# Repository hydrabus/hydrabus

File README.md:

HydraBus
========

HydraBus an open source multi-tool hardware

You can Buy HydraBus/HydraNFC Online: http://hydrabus.com/buy-online

Wiki Getting Started: https://github.com/hydrabus/hydrafw/wiki/Getting-Started-with-HydraBus

HydraFW official firmware for Hydrabus
========

Wiki for HydraFW: https://github.com/hydrabus/hydrafw/wiki

See https://github.com/hydrabus/hydrafw

To build hydrafw see instructions here: 
* Windows: https://github.com/hydrabus/hydrafw/wiki/how-to-build-flash-and-use-hydrafw-on-windows
* Linux: https://github.com/hydrabus/hydrafw/wiki/how-to-build-flash-and-use-hydrafw-on-linux

Official Micro Python port for HydraBus
========
See https://github.com/micropython/micropython
Tested with GCC ARM 4.9 2015q3(GNU_ARM_4_9_2015q3) 
* See https://github.com/hydrabus/hydrafw_hydranfc_shield_v2/wiki `How to Build/Flash/Use HydraFW` for more details

To build micropython for HydraBus do:

    git clone --recursive https://github.com/micropython/micropython
    cd micropython/ports/stm32
    make BOARD=HYDRABUS

* At end of build you shall have:
 * GEN build-HYDRABUS/firmware.dfu
 * GEN build-HYDRABUS/firmware.hex
* In order to flash the *.dfu follow steps here: https://github.com/hydrabus/hydrafw/wiki/Getting-Started-with-HydraBus

For more details on official micropython hydrabus port see: https://github.com/micropython/micropython/tree/master/ports/stm32/boards/HYDRABUS

Official Black Magic JTAG/SWD debugger port for HydraBus
========
See https://github.com/blacksphere/blackmagic.git

Before to build the firmware check this issue (as you need a new GCC ARM Compiler >=4.9): https://github.com/blacksphere/blackmagic/issues/128
Tested with GCC ARM 4.9 2015q3(GNU_ARM_4_9_2015q3)
* See working version for reference blackmagic_branch_hydrabus_Firmware 1.5-00319-g49390fe-dirty.zip:
  * https://github.com/hydrabus/hydrabus/files/11436416/blackmagic_branch_hydrabus_Firmware.1.5-00319-g49390fe-dirty.zip
* Note: Latest version of blackmagic have "Device failed enumeration" issue see https://github.com/hydrabus/hydrabus/issues/4
* See https://github.com/hydrabus/hydrafw_hydranfc_shield_v2/wiki `How to Build/Flash/Use HydraFW` for more details

To build Black Magic for HydraBus do:

    git clone --recursive https://github.com/blacksphere/blackmagic.git
    cd blackmagic
    make PROBE_HOST=hydrabus

* At end of build you shall have:
 * OBJCOPY blackmagic.bin
 * OBJCOPY blackmagic.hex
 * Creating blackmagic.dfu
* In order to flash the *.dfu follow steps here: https://github.com/bvernoux/hydrafw/wiki/Getting-Started-with-HydraBus

For more details on official blackmagic hydrabus port see:
https://github.com/blacksphere/blackmagic/tree/master/src/platforms/hydrabus

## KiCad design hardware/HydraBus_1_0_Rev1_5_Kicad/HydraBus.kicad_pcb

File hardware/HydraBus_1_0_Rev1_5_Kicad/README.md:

HydraBus Schematic and Board KiCad (6.0.11)
========

This directory contains HydraBus Schematic and Board for KiCad (6.0.11)

HydraBus: Hardware license [CC BY-NC 4.0](https://creativecommons.org/licenses/by-nc/4.0/) (for commercial license contact info@hydrabus.com)

For more details on the hardware see also http://hydrabus.com/hydrabus-1-0-specifications

Revision 1.5 (vs Rev 1.4)
- HydraBus v1 Rev1.5 is designed under KiCad 6.0.11
- Replaced 2x microUSB connectors by 2x USB Female Type C connectors (Korean Hroparts Elec TYPE-C-31-M-12)
- Replacement of ESD protections (as old ones are obsolete)

To summarize there is no any functional change between HydraBus v1 Rev1.5 and previous versions

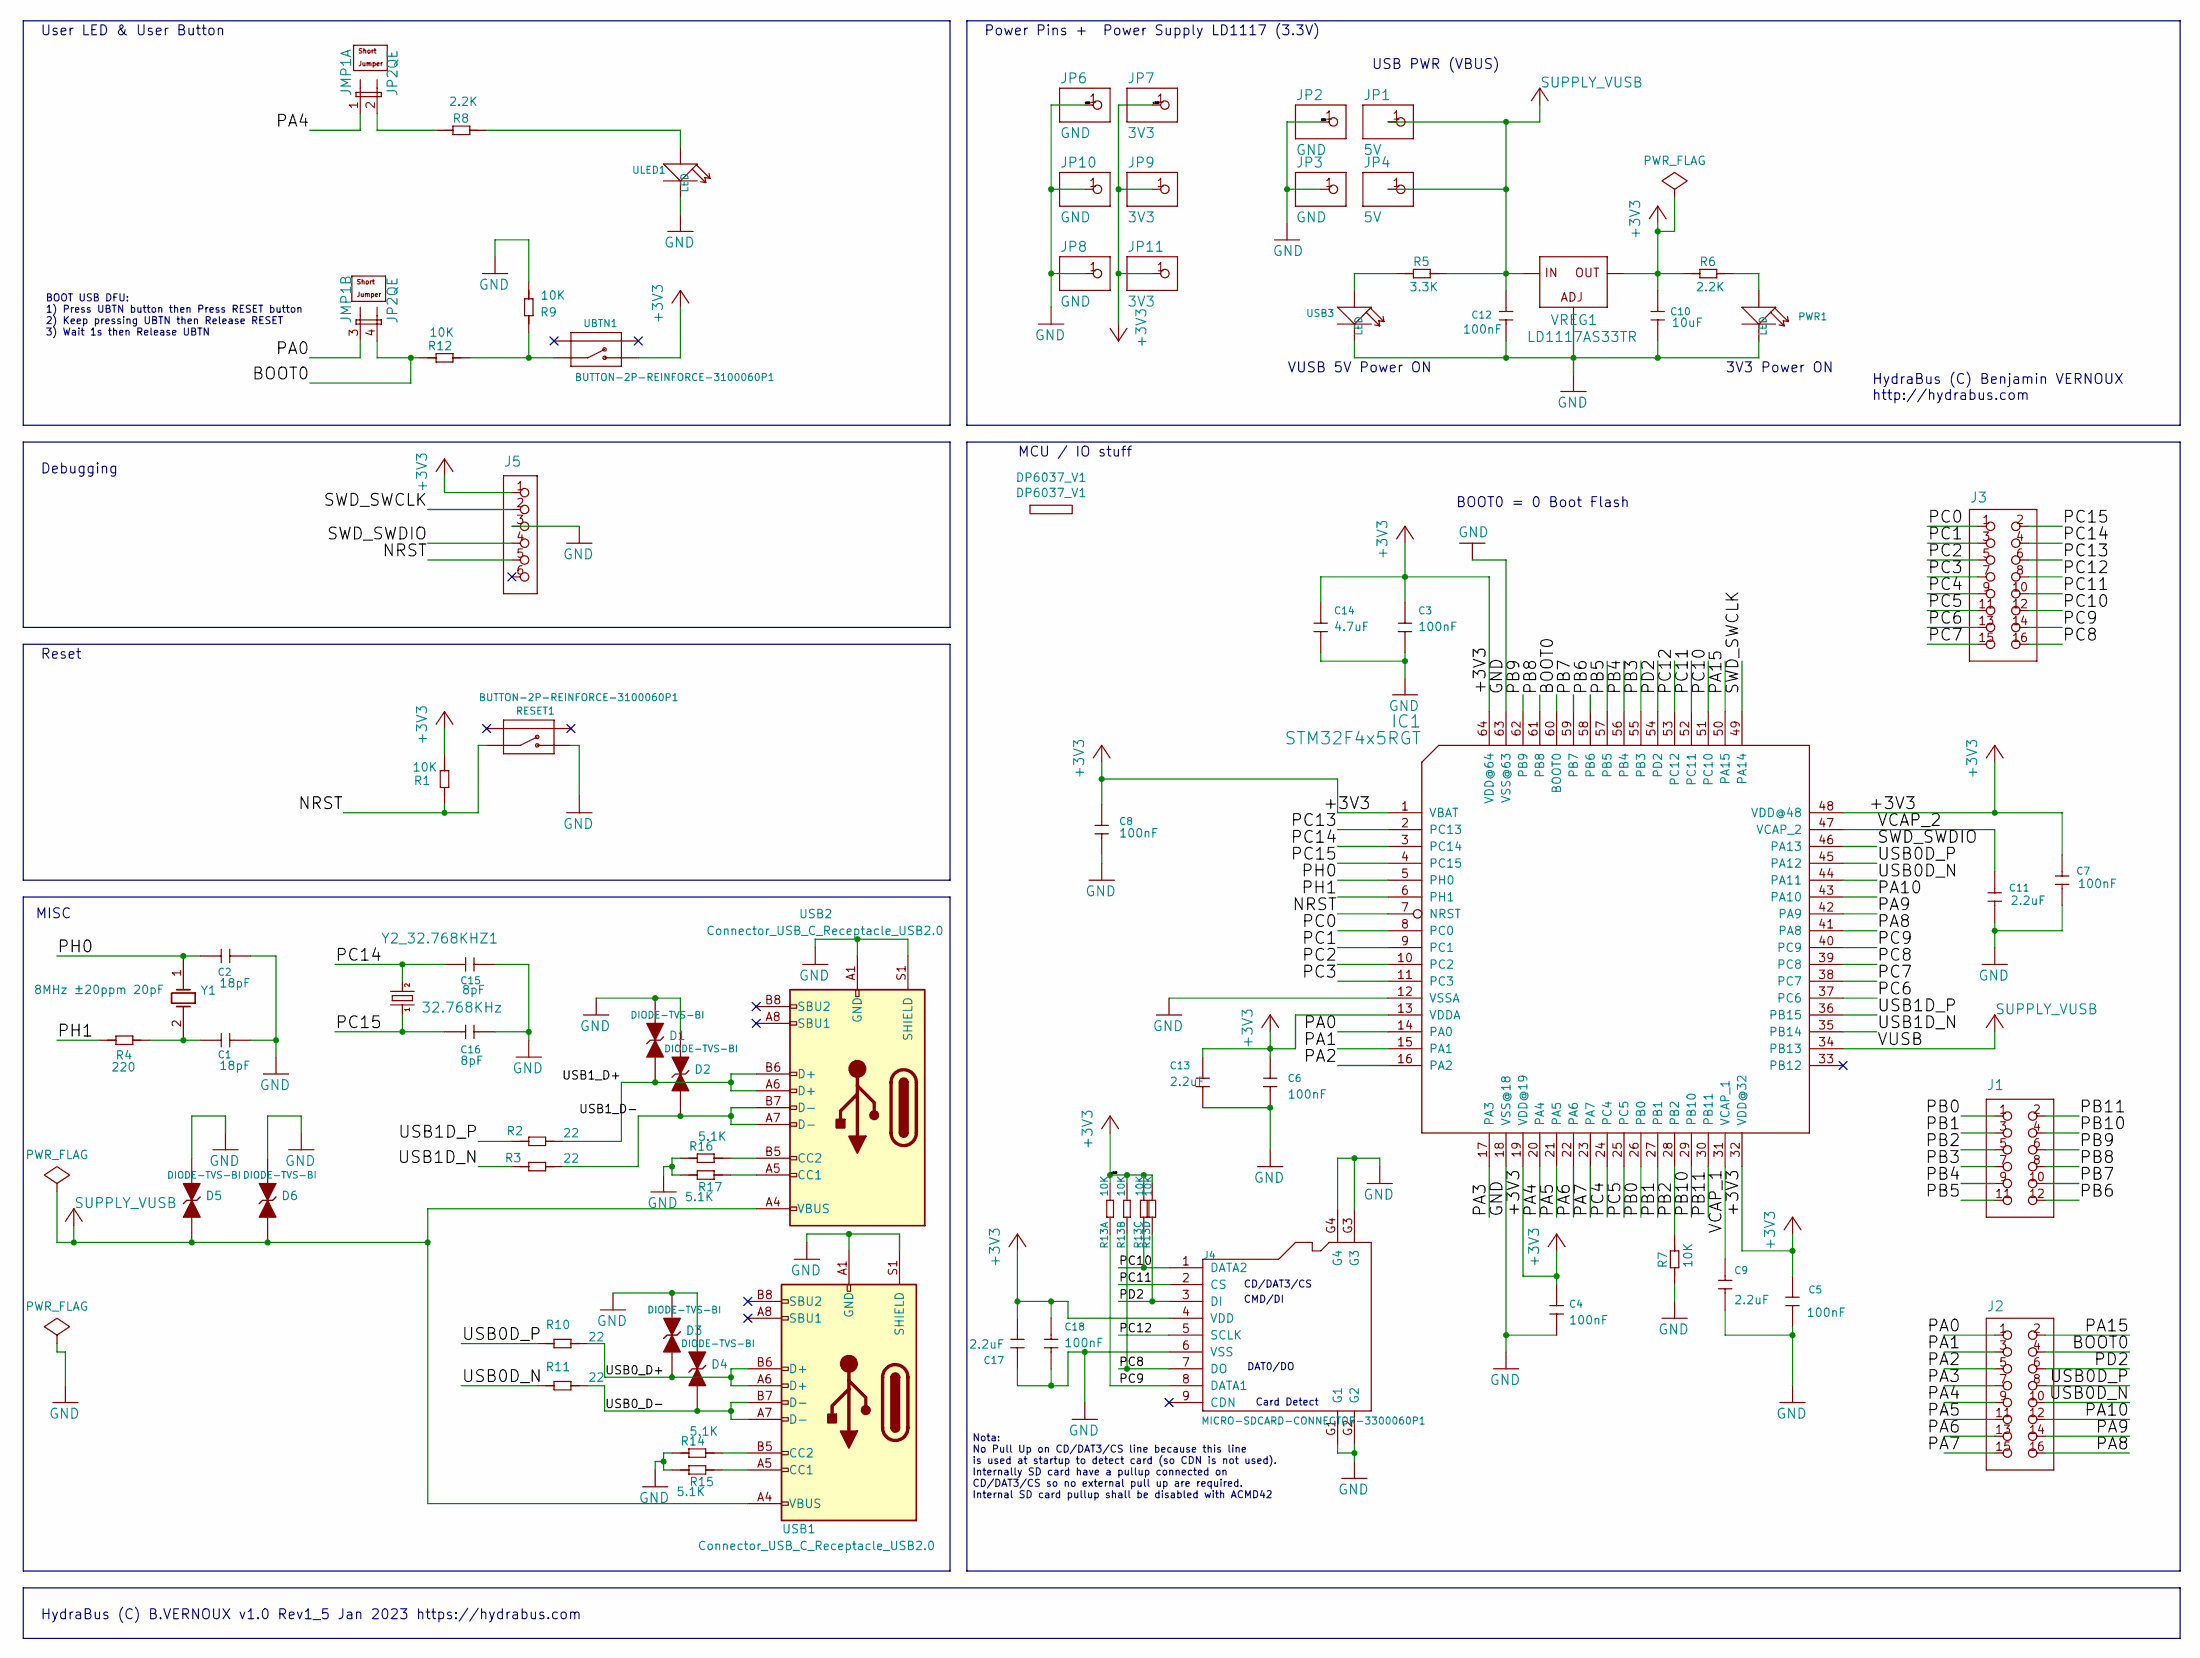
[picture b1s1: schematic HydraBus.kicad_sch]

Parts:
C1, C2: 18pF; C0603; LCSC_Part C1647
C3, C4, C5, C6, C7, C8, C12, C18: 100nF; C0603; LCSC_Part C14663
C9, C11, C13, C17: 2.2uF; C0603; LCSC_Part C23630
C10: 10uF; C0805; LCSC_Part C15850
C14: 4.7uF; C0603; LCSC_Part C19666
C15, C16: 8pF; C0603
D1, D2, D3, D4, D5, D6: DIODE-TVS-BI; 0402; LCSC_Part C191267
DP6037_V1: DP6037_V1
IC1: STM32F4x5RGT; LQFP64; LCSC_Part C15742
J1: CON_HEADER_2X07; M2X6; LCSC_Part PRPC007DFBN-RC
J2, J3: CON_HEADER_2X10; M2X8; LCSC_Part PRPC010DFBN-RC
J4: MICRO-SDCARD-CONNECTOR-3300060P1; 9P-SMD-W-RING; LCSC_Part C341092
J5: CON_HEADER_1X06-PTH; M1X6; LCSC_Part PEC06SFBN
JMP1: JP2QE; JP2Q
JMP_UBTN1: SHORT-JUMPER-2P-3460440P1; 2P-2.54
JMP_ULED1: SHORT-JUMPER-2P-3460440P1; 2P-2.54
JP1, JP4: 5V; 1X01
JP2, JP3, JP6, JP8, JP10: GND; 1X01
JP7, JP9, JP11: 3V3; 1X01
PWR1: LED; LED0603; LCSC_Part C72043
R1, R7, R9, R12: 10K; R0603; LCSC_Part C25804
R2, R3, R10, R11: 22; R0603; LCSC_Part C23345
R4: 220; R0603; LCSC_Part C22962
R5: 3.3K; R0603; LCSC_Part C22978
R6, R8: 2.2K; R0603; LCSC_Part C4190
R13: 10K; R1206-8; LCSC_Part C29718
R14, R15, R16, R17: 5.1K; R0603; LCSC_Part C23186
RESET1: BUTTON-2P-REINFORCE-3100060P1; 4P-SMD-7.0X3.5X3.5H-90D
UBTN1: BUTTON-2P-REINFORCE-3100060P1; 4P-SMD-7.0X3.5X3.5H-90D
ULED1: LED; LED0603; LCSC_Part C72043
USB1, USB2: Connector_USB_C_Receptacle_USB2.0; TYPE-C-31-M-12; LCSC_Part C165948
USB3: LED; LED0603; LCSC_Part C72043
VREG1: LD1117AS33TR; SOT223; LCSC_Part C115288
Y1: SMD-5032_2P_8MHz_20ppm_20pF; SMD-5032_2P; LCSC_Part C115962
Y2_32.768KHZ1: 32.768KHz; TC38H

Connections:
/BOOT0: IC1.60 (BOOT0), J2.4, JMP1.4 (2), R12.2
/NRST: IC1.7 (NRST), J5.5, R1.1, RESET1.1
/PA0: IC1.14 (PA0), J2.1, JMP1.3 (1)
/PA1: IC1.15 (PA1), J2.3
/PA2: IC1.16 (PA2), J2.5
/PA3: IC1.17 (PA3), J2.7
/PA4: IC1.20 (PA4), J2.9, JMP1.1
/PA5: IC1.21 (PA5), J2.11
/PA6: IC1.22 (PA6), J2.13
/PA7: IC1.23 (PA7), J2.15
/PA8: IC1.41 (PA8), J2.16
/PA9: IC1.42 (PA9), J2.14
/PA10: IC1.43 (PA10), J2.12
/PA15: IC1.50 (PA15), J2.2
/PB0: IC1.26 (PB0), J1.1
/PB1: IC1.27 (PB1), J1.3
/PB2: IC1.28 (PB2), J1.5, R7.1
/PB3: IC1.55 (PB3), J1.7
/PB4: IC1.56 (PB4), J1.9
/PB5: IC1.57 (PB5), J1.11
/PB6: IC1.58 (PB6), J1.12
/PB7: IC1.59 (PB7), J1.10
/PB8: IC1.61 (PB8), J1.8
/PB9: IC1.62 (PB9), J1.6
/PB10: IC1.29 (PB10), J1.4
/PB11: IC1.30 (PB11), J1.2
/PC0: IC1.8 (PC0), J3.1
/PC1: IC1.9 (PC1), J3.3
/PC2: IC1.10 (PC2), J3.5
/PC3: IC1.11 (PC3), J3.7
/PC4: IC1.24 (PC4), J3.9
/PC5: IC1.25 (PC5), J3.11
/PC6: IC1.37 (PC6), J3.13
/PC7: IC1.38 (PC7), J3.15
/PC8: IC1.39 (PC8), J3.16, J4.7 (DO), R13.2 (1)
/PC9: IC1.40 (PC9), J3.14, J4.8 (DATA1), R13.1
/PC10: IC1.51 (PC10), J3.12, J4.1 (DATA2), R13.3 (1)
/PC11: IC1.52 (PC11), J3.10, J4.2 (CS)
/PC12: IC1.53 (PC12), J3.8, J4.5 (SCLK)
/PC13: IC1.2 (PC13), J3.6
/PC14: C15.1, IC1.3 (PC14), J3.4, Y2_32.768KHZ1.2
/PC15: C16.1, IC1.4 (PC15), J3.2, Y2_32.768KHZ1.1
/PD2: IC1.54 (PD2), J2.6, J4.3 (DI), R13.4 (1)
/PH0: C2.1, IC1.5 (PH0), Y1.1 (OSC1)
/PH1: IC1.6 (PH1), R4.2
/SWD_SWCLK: IC1.49 (PA14), J5.2
/SWD_SWDIO: IC1.46 (PA13), J5.4
/USB0D_N: IC1.44 (PA11), J2.10, R11.2
/USB0D_P: IC1.45 (PA12), J2.8, R10.2
/USB0_D+: D3.1 (A), R10.1, USB1.A6 (D+), USB1.B6 (D+)
/USB0_D-: D4.1 (A), R11.1, USB1.A7 (D-), USB1.B7 (D-)
/USB1D_N: IC1.35 (PB14), R3.2
/USB1D_P: IC1.36 (PB15), R2.2
/USB1_D+: D1.1 (A), R2.1, USB2.A6 (D+), USB2.B6 (D+)
/USB1_D-: D2.1 (A), R3.1, USB2.A7 (D-), USB2.B7 (D-)
/VCAP_1: C9.2, IC1.31 (VCAP_1)
/VCAP_2: C11.1, IC1.47 (VCAP_2)
unnamed: C1.1, R4.1, Y1.2 (OSC2)
unnamed: JMP1.2, R8.2
unnamed: PWR1.+, R6.1
unnamed: R5.2, USB3.+
unnamed: R8.1, ULED1.+
unnamed: R9.1, R12.1, UBTN1.1
unnamed: R14.1, USB1.B5 (CC2)
unnamed: R15.2, USB1.A5 (CC1)
unnamed: R16.1, USB2.B5 (CC2)
unnamed: R17.2, USB2.A5 (CC1)
VBUS: C12.1, D5.1 (A), D6.1 (A), IC1.34 (PB13), JP1.1, JP4.1, R5.1, USB1.A4 (VBUS), USB1.A9 (VBUS), USB1.B4 (VBUS), USB1.B9 (VBUS), USB2.A4 (VBUS), USB2.A9 (VBUS), USB2.B4 (VBUS), USB2.B9 (VBUS), VREG1.3 (IN)

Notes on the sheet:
Debugging
BOOT USB DFU: 1) Press UBTN button then Press RESET button 2) Keep pressing UBTN then Release RESET 3) Wait 1s then Release UBTN
Card Detect
HydraBus (C) Benjamin VERNOUX http://hydrabus.com
MCU / IO stuff
BOOT0 = 0 Boot Flash
3V3 Power ON
USB PWR (VBUS)
CMD/DI
VUSB 5V Power ON
CD/DAT3/CS
User LED & User Button
Reset
HydraBus (C) B.VERNOUX v1.0 Rev1_5 Jan 2023 https://hydrabus.com
Power Pins + Power Supply LD1117 (3.3V)
DAT0/DO
Nota: No Pull Up on CD/DAT3/CS line because this line is used at startup to detect card (so CDN is not used). Internally SD card have a pullup connected on CD/DAT3/CS so no external pull up are required. Internal SD card pullup shall be disabled with ACMD42
MISC

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
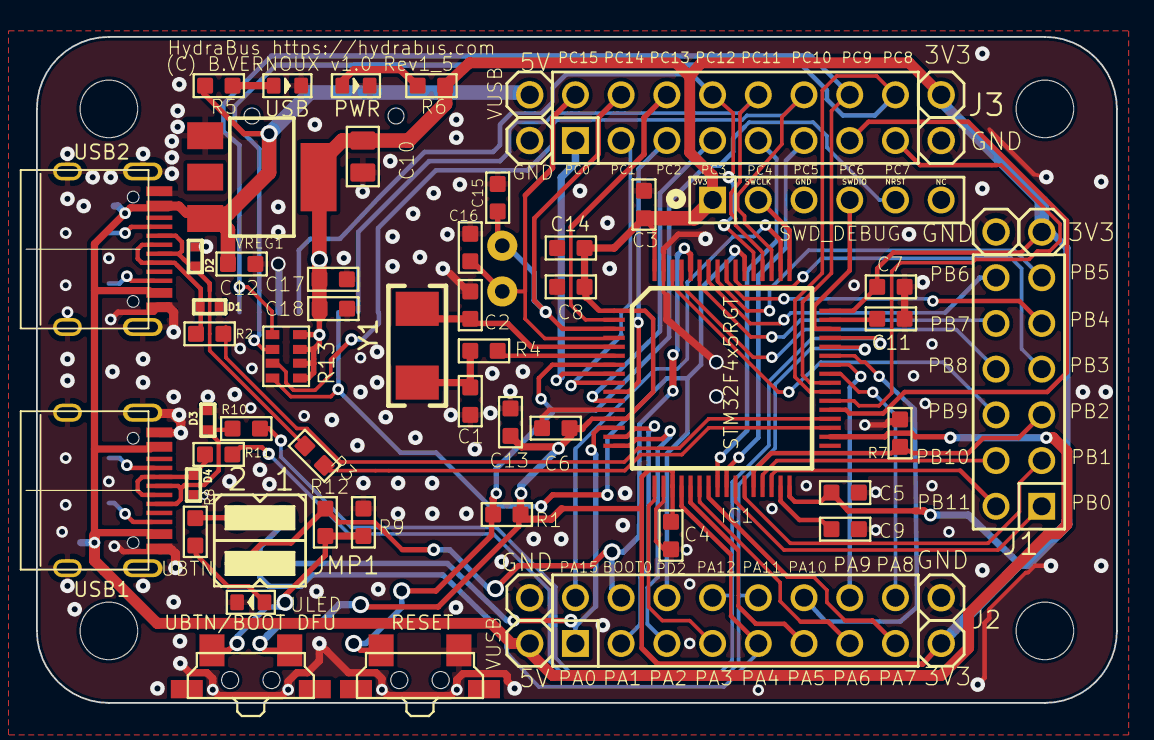
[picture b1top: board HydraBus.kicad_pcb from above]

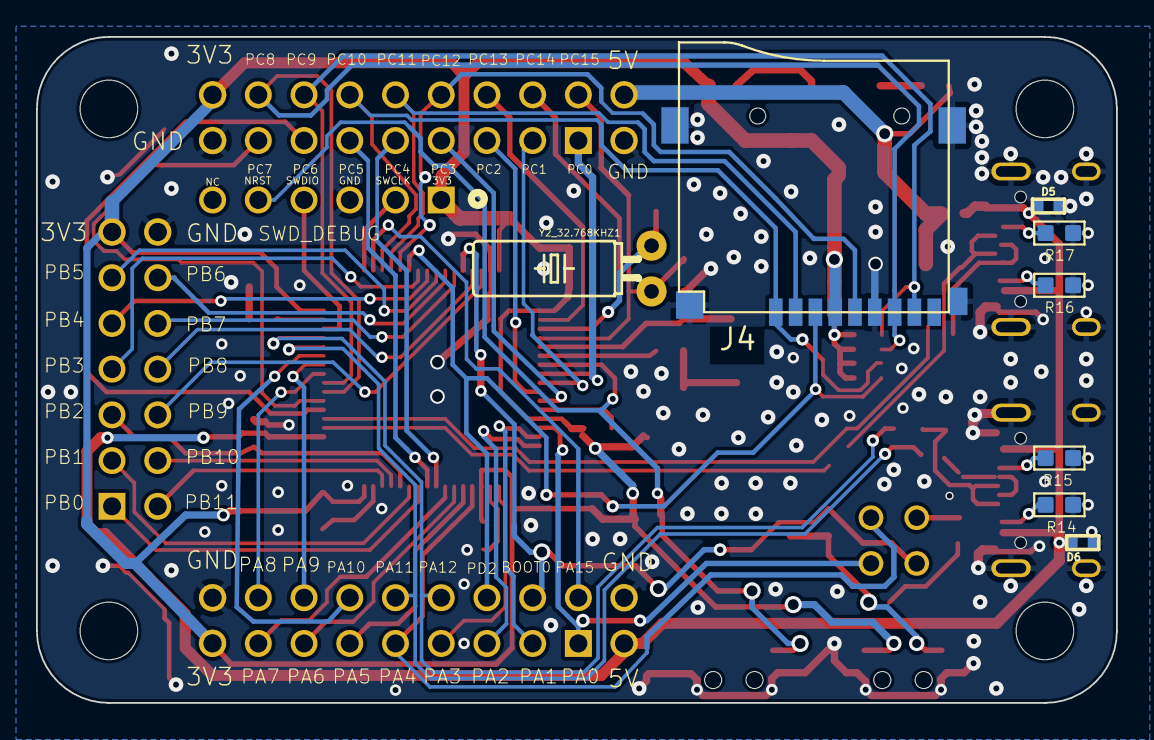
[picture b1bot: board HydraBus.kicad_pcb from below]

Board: 2 copper layers, 60.0 x 37.0 mm, 71 parts (8 on the bottom side), 70 nets.

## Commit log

2014-04-20 gitmodules update
2014-05-28 Update gitmodules
2014-05-28 Cleanup
2014-05-28 Cleanup gitmodule and added chibios 2.6.x
2014-06-02 HydraBus board
2014-06-22 Moved project/firmware to firmware directory
2014-09-11 HydraBus hardware files Eagle, PDF, xls ...
2014-09-11 Added MicroPython binary for HydraBus and instructions to flash it through USB DFU on HydraBus.
2014-09-11 Added board
2014-09-21 HydraFW first import version 0.1Beta
2014-09-21 Add picture for HydraBus to enter in USB DFU mode
2014-09-29 Update firmware from with last commit https://github.com/bvernoux/micropython/commit/41249e17c3a661dc36f49ff6156ce67a70466157
2014-09-30 HydraBus1.0 Sick Of Beige Case
2014-09-30 Windows XP, Vista, 7 and 8 drivers for HydraBus firmware USB CDC Virtual Serial Port.
2014-09-30 HydraBus1.0 Pin & Pin Assignment updated.
2014-10-01 Fix typo
2014-10-02 Added HydraBus Pins Assignment
2014-10-06 Add micropython firmware source as submodule.
2014-10-06 Add micropython firmware source as submodule and update with latest micropython.
2014-10-06 Cleanup Submodule micropython
2014-10-06 Add latest micropython as submodule
2014-10-06 Update micropython firmware to latest v1.3.3-31-g9c6f737
2014-10-07 Fixo typo thanks to Philippe Teuwen
    Update towards Philippe Teuwen wiki
    http://wiki.yobi.be/wiki/HydraNFC
2014-10-07 Fix for Debian... also exclude ModemManager thanks to Philippe Teuwen
2014-10-07 Fix typo thanks to Philippe Teuwen
    Update towards http://wiki.yobi.be/wiki/HydraNFC "Getting ready to use HydraBus" & "Using HydraBus"
2014-10-08 Cleanup, update configuration/conf and update microrl submodule.
2014-10-09 directory hydrafw deleted/replaced by submodule hydrafw
2014-10-10 Update hydrafw
2014-10-11 Added link to Wiki HydraFW
2014-10-13 Removed STM32F4_USB_DFU_Driver.zip
2014-10-22 Added HydraBus_1_0_HydraFW_Default_PinAssignment.odg/.pdf Fixed and update of HydraBus_1_0_PinAssignment.odg/.pdf
2014-10-22 Add A4 version of HydraBus_1_0_HydraFW_Default_PinAssignment
2014-10-22 Update link to latest hydrafw
2014-10-22 Updated submodule micropython to latest version
2014-10-22 update micropython firmware.dfu to latest version => Micro Python v1.3.3-113-g5fc42a6
2014-12-01 Added HydraBus Basic Pin Assignment
2014-12-26 Update micropython to latest Micro Python v1.3.3-340-gc55a4d8
2014-12-26 Update micropython to latest Micro Python v1.3.7-96-gc55a4d8
2014-12-26 Update hydrafw to latest version v0.4-beta-23-ge68b10a
2015-01-01 Updated Default Pin Assignment A4 and removed the old not A4.
2015-01-13 Added blackmagic port for HydraBus
2016-02-04 HydraBus v1.0 Rev1_2 Release (CadSoft Eagle v7.1 files + BOM + Schematic + Gerber)
2016-04-20 Update Black Magic official hydrabus port
2016-04-22 removed firmware link (obsolete)
2016-04-22 removed firmware link/submodule (obsolete)
2016-05-31 Add HydraBus_1_0_Shield_Template_Rev0 Kicad link
2016-12-06 HydraBus V1.0 Rev1.2+
2016-12-18 Update of links replaced bvernoux to hydrabus
2017-03-27 Create LICENSE
2017-08-03 HydraBus V1.0 Rev1.3
2018-10-03 Update official micropython hydrabus port link
2018-12-29 Updated pin assignment diagrams
2018-12-29 Removed GND/VCC arrows
2019-12-27 Updated 26 Dec 2019 with https://www.seeedstudio.com/opl.html
2020-05-14 Import HydraBus v1.0 Rev1.4 done with KiCad (5.1.5)-2
2020-05-14 Update adding HydraBus_1_0_Rev1_4
2020-08-29 Update HydraBus_board.jpg with latest HydraBus v1.0 Rev1.4 board photo
2024-01-01 Add HydraBus v1.0 Rev1.5 Schematic/Board Hardware license CC BY-NC 4.0 (KiCad 6.0.11) Update HydraBus_1_0_HydraFW_Basic_PinAssignment & HydraBus_1_0_HydraFW_Default_PinAssignment_A4 with latest Hydra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
2024-01-01 Update README.md with pictures with latest HydraBus v1.0 Rev1.5 board (USB Type C)
2024-01-03 Minor fixes / improvements on Default & Basic PinAssignment
2024-03-16 Add HydraBus_v1_0_Rev1_SoBv1_DP6037-Top_Bottom (Top is same as Bottom) in DXF & STL format
